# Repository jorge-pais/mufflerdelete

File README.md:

# Muffler Delete
Guitar distortion/fuzz effect based on the 72' Triangle Big Muff, featuring an alternate clipping mode using LEDs and a seperate boost circuit.

## Circuit Schematic

## 3D Board View

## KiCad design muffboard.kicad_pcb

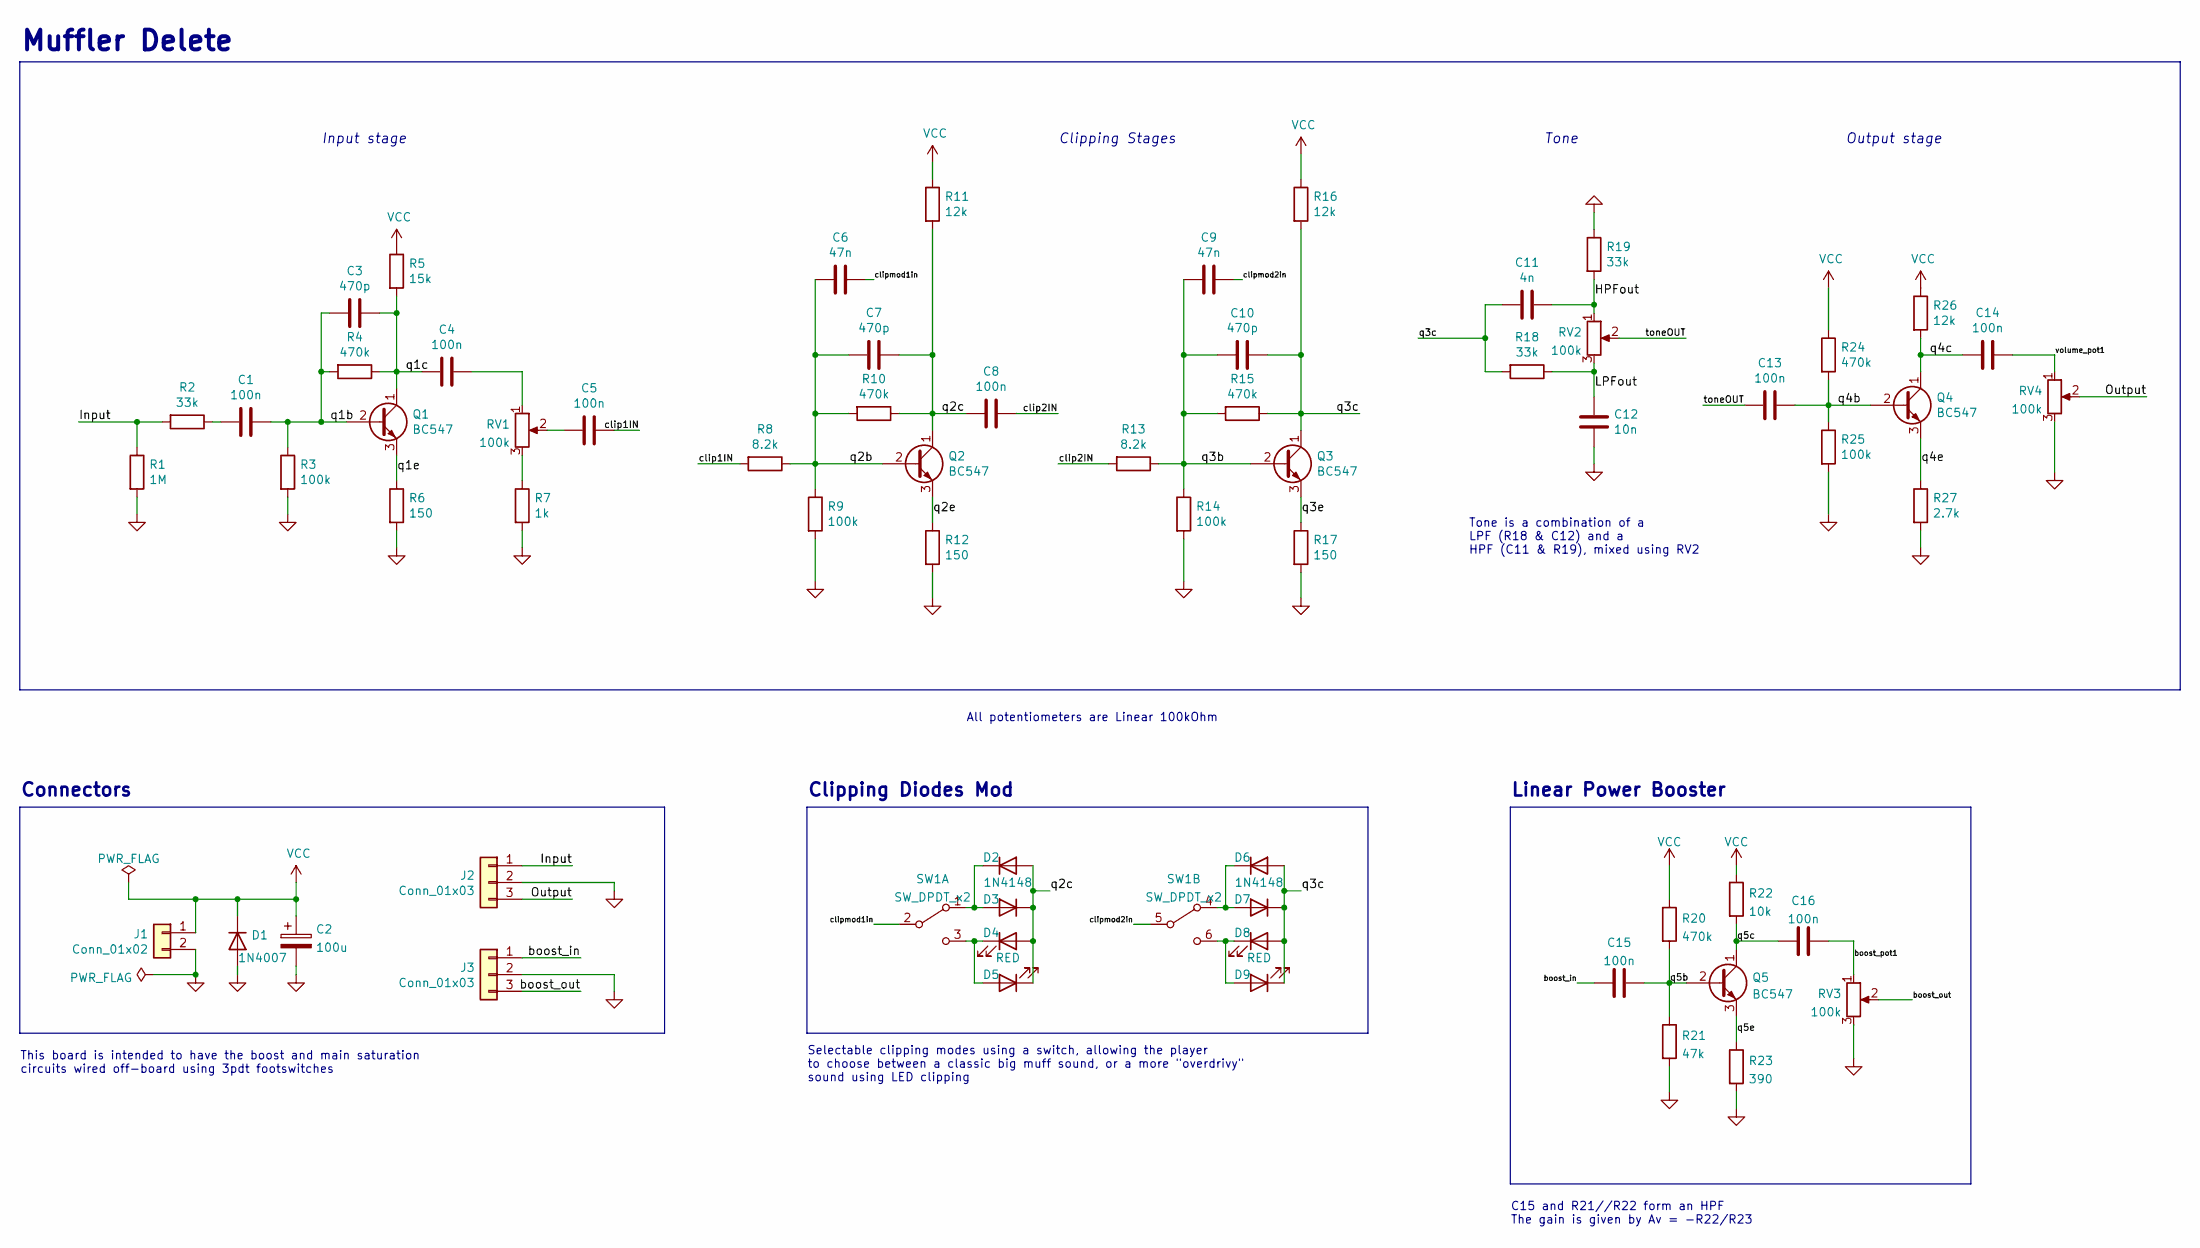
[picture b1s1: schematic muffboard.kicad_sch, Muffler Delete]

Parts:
C1, C4, C5, C8, C13, C14, C15, C16: 100n; C_Rect_L7.2mm_W2.5mm_P5.00mm_FKS2_FKP2_MKS2_MKP2
C2: 100u; CP_Radial_D6.3mm_P2.50mm
C3, C7, C10: 470p; C_Rect_L7.2mm_W2.5mm_P5.00mm_FKS2_FKP2_MKS2_MKP2
C6, C9: 47n; C_Rect_L7.2mm_W2.5mm_P5.00mm_FKS2_FKP2_MKS2_MKP2
C11: 4n; C_Rect_L7.2mm_W2.5mm_P5.00mm_FKS2_FKP2_MKS2_MKP2
C12: 10n; C_Rect_L7.2mm_W2.5mm_P5.00mm_FKS2_FKP2_MKS2_MKP2
D1: 1N4007; D_DO-41_SOD81_P10.16mm_Horizontal
D2, D3, D6, D7: 1N4148; D_DO-35_SOD27_P7.62mm_Horizontal
D4, D5, D8, D9: RED; LED_D3.0mm
J1: Conn_01x02; PinHeader_1x02_P2.54mm_Vertical
J2, J3: Conn_01x03; PinHeader_1x03_P2.54mm_Vertical
Q1, Q2, Q3, Q4, Q5: BC547; TO-92_Inline_Wide
R1: 1M; R_Axial_DIN0207_L6.3mm_D2.5mm_P7.62mm_Horizontal
R2, R18, R19: 33k; R_Axial_DIN0207_L6.3mm_D2.5mm_P7.62mm_Horizontal
R3, R9, R14, R25: 100k; R_Axial_DIN0207_L6.3mm_D2.5mm_P7.62mm_Horizontal
R4, R10, R15, R20, R24: 470k; R_Axial_DIN0207_L6.3mm_D2.5mm_P7.62mm_Horizontal
R5: 15k; R_Axial_DIN0207_L6.3mm_D2.5mm_P7.62mm_Horizontal
R6, R12, R17: 150; R_Axial_DIN0207_L6.3mm_D2.5mm_P7.62mm_Horizontal
R7: 1k; R_Axial_DIN0207_L6.3mm_D2.5mm_P7.62mm_Horizontal
R8, R13: 8.2k; R_Axial_DIN0207_L6.3mm_D2.5mm_P7.62mm_Horizontal
R11, R16, R26: 12k; R_Axial_DIN0207_L6.3mm_D2.5mm_P7.62mm_Horizontal
R21: 47k; R_Axial_DIN0207_L6.3mm_D2.5mm_P7.62mm_Horizontal
R22: 10k; R_Axial_DIN0207_L6.3mm_D2.5mm_P7.62mm_Horizontal
R23: 390; R_Axial_DIN0207_L6.3mm_D2.5mm_P7.62mm_Horizontal
R27: 2.7k; R_Axial_DIN0207_L6.3mm_D2.5mm_P7.62mm_Horizontal
RV1, RV2, RV3, RV4: 100k; Potentiometer_Omeg_PC16BU_Vertical
SW1: SW_DPDT_x2; SW_E-Switch_EG1271_DPDT

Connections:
/HPFout: C11.1, R19.2, RV2.1
/Input: J2.1, R1.1, R2.2
/LPFout: C12.1, R18.1, RV2.3
/Output: J2.3, RV4.2
/boost_in: C15.1, J3.1
/boost_out: J3.3, RV3.2
/boost_pot1: C16.2, RV3.1
/clip1IN: C5.1, R8.2
/clip2IN: C8.1, R13.2
/clipmod1in: C6.1, SW1.2 (B)
/clipmod2in: C9.1, SW1.5 (B)
/q1b: C1.1, C3.2, Q1.2 (B), R3.1, R4.2
/q1c: C3.1, C4.2, Q1.1 (C), R4.1, R5.2
/q1e: Q1.3 (E), R6.1
/q2b: C6.2, C7.2, Q2.2 (B), R8.1, R9.1, R10.2
/q2c: C7.1, C8.2, D2.2 (A), D3.1 (K), D4.2 (A), D5.1 (K), Q2.1 (C), R10.1, R11.2
/q2e: Q2.3 (E), R12.1
/q3b: C9.2, C10.2, Q3.2 (B), R13.1, R14.1, R15.2
/q3c: C10.1, C11.2, D6.2 (A), D7.1 (K), D8.2 (A), D9.1 (K), Q3.1 (C), R15.1, R16.2, R18.2
/q3e: Q3.3 (E), R17.1
/q4b: C13.2, Q4.2 (B), R24.2, R25.1
/q4c: C14.2, Q4.1 (C), R26.2
/q4e: Q4.3 (E), R27.1
/q5b: C15.2, Q5.2 (B), R20.2, R21.1
/q5c: C16.1, Q5.1 (C), R22.2
/q5e: Q5.3 (E), R23.1
/toneOUT: C13.1, RV2.2
/volume_pot1: C14.1, RV4.1
GND: C2.2, C12.2, D1.2 (A), J1.2, J2.2, J3.2, R1.2, R3.2, R6.2, R7.2, R9.2, R12.2, R14.2, R17.2, R19.1, R21.2, R23.2, R25.2, R27.2, RV3.3, RV4.3
unnamed: C1.2, R2.1
unnamed: C4.1, RV1.1
unnamed: C5.2, RV1.2
unnamed: D2.1 (K), D3.2 (A), SW1.1 (A)
unnamed: D4.1 (K), D5.2 (A), SW1.3 (C)
unnamed: D6.1 (K), D7.2 (A), SW1.4 (A)
unnamed: D8.1 (K), D9.2 (A), SW1.6 (C)
unnamed: R7.1, RV1.3
VCC: C2.1, D1.1 (K), J1.1, R5.1, R11.1, R16.1, R20.1, R22.1, R24.1, R26.1

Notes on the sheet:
Connectors
Muffler Delete
Selectable clipping modes using a switch, allowing the player to choose between a classic big muff sound, or a more "overdrivy" sound using LED clipping
Clipping Stages
Input stage
Output stage
Clipping Diodes Mod
Tone
This board is intended to have the boost and main saturation circuits wired off-board using 3pdt footswitches
All potentiometers are Linear 100kOhm
Tone is a combination of a LPF (R18 & C12) and a HPF (C11 & R19), mixed using RV2
Linear Power Booster
C15 and R21//R22 form an HPF The gain is given by Av = -R22/R23

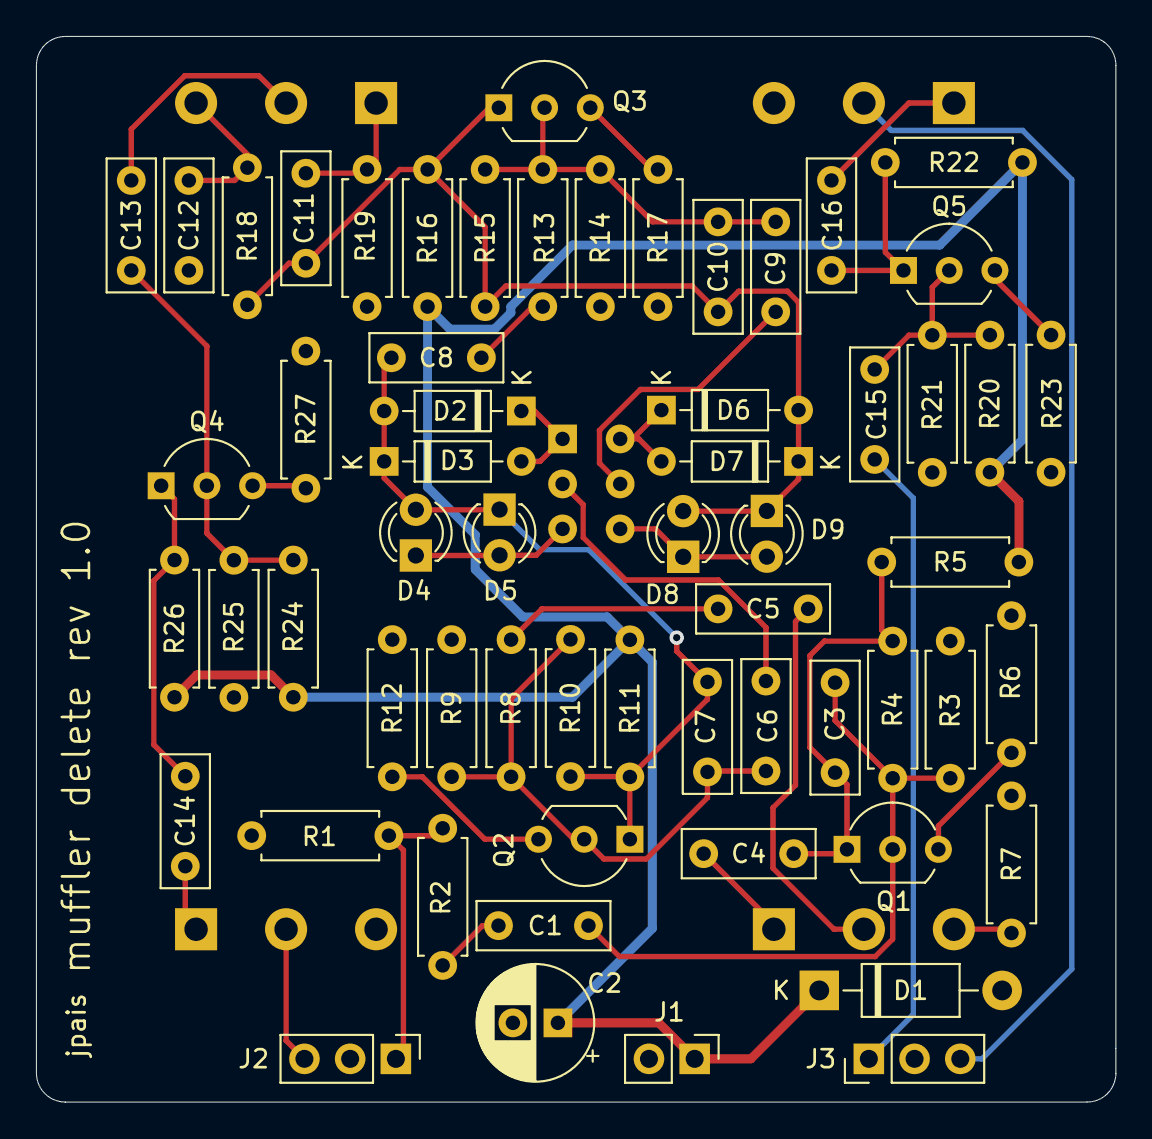
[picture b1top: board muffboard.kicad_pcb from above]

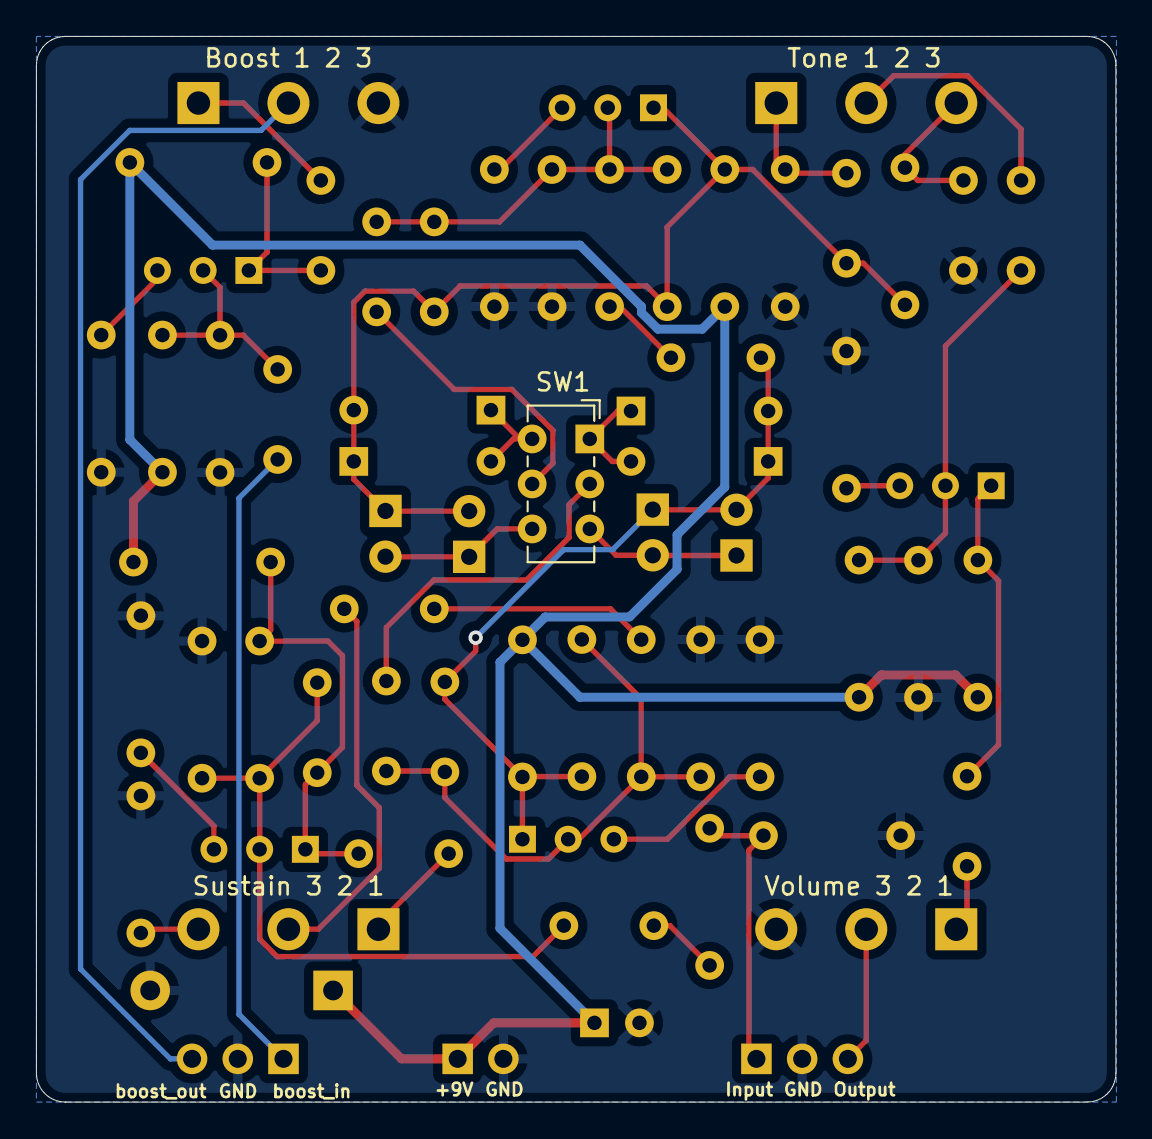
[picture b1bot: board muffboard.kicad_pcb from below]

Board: 2 copper layers, 60.0 x 59.2 mm, 65 parts (5 on the bottom side), 38 nets.

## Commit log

2022-03-01 removed useless files
2022-03-01 initial component placing on pcb
2022-03-01 finished board (de estoura)
2022-03-02 added BOM and schematic pdf
2022-03-02 rev 1.0 board
2022-03-02 deleted cache file
2022-03-02 Edit pcb
2022-04-13 Added LICENSE.md
